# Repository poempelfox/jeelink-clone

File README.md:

# Foxis JeeLink-clone

## Intro

JeeLinks are transceivers with a microcontroller, that can be
attached to the USB port of a PC. They were designed many
years ago by JeeLabs a.k.a. Jean-Claude Wippler, and like all
of the (many!) cool designs on his now sadly defunct weblog
under jeelabs.org, they were completely Open-Source-Hardware -
while there was a webshop where you could buy ready-made
JeeLinks if you were lazy, you could also just build them
yourself, or modify the designs.

I use many JeeLinks as receivers for my various "FoxTemp"
sensors like foxtemp2016 or foxtemp2024. For that, the
JeeLink is flashed with the "LaCrosse" sketch developed
by the FHEM project (with one minor source code modification
needed to adapt the settings) and attached to a PC, where
a little deamon makes the received data available for query
via network.

Unfortunately, by now jeelabs.org is completely defunct and
you can only access the treasure trove of information that used
to be hosted there through archive.org. The webshop is still
there, but it is in the UK - and thanks to Brexit, ordering
from there to mainland Europe promises to be so painful that
I want to avoid it at all cost.

So where do I get my JeeLinks now?
Well the plan is to do what I've been doing a lot recently:
Design a PCB with mostly SMD components on one side, and
send it off to china for fabrication. And you may ask,
"Wait, doesn't that have the same problems as ordering
from the UK?", and of course in both cases it means crossing
the border from outside the EU into the EU taxation and
customs union. The difference is that the chinese fab
is registered as a so called IOSS, Import One Stop Shop.
That means (as of July 2024) that for any orders below 150
Euro the shop will directly collect the applicable VAT
and transfer it to EU customs. As orders below 150 Euro
are exempt from taxes other than VAT, that means everything
has already been paid when your parcel enters the EU.
And that makes a huge difference, because most parcel services
massively rip you off with the tax handling. For example,
DHL Express will charge a "Kapitalbereitstellungs-
Provision" of (at least) a whopping 14.88 Euros, even if
there was just a single cent of VAT to be paid for the
import, for borrowing you the money for two days. It's
also not possible to opt out of their shitty disservice
and just collect the parcel yourself at the next customs
office. But if there is no VAT or other taxes to be
paid, your parcel just arrives without the ripoff.

Note that this is NOT a full JeeLink clone. My goal
was to have something that works with the FHEM-LaCrosse-
Sketch so I don't have to touch that firmware. But
apart from that, I saw no reason to stay too true to
the original,  so a few modifications have been made:
- proper JeeLinks also have an extra 16 Mbit flash
  memory chip. That is not used by the LaCrosse sketch,
  so I left it out.
- JeeLinks have an ultrabright blue LED that massively
  annoyed me (I don't like getting blind from accidently
  looking at the stick. I also don't need it to
  illuminate the whole room.), so it was replaced with
  a very ordinary and certainly not ultrabright yellow
  LED.
- this did not import the old design files (which were
  in a very old Eagle file format that I couldn't get
  imported) and instead started from scratch in Kicad,
  so the positioning of things like LEDs is entirely
  different.
- When these things come from the factory, they have
  no bootloader that would permit programming them via
  USB yet. So we need to use ISP, but a normal-sized ISP
  connector is way too large to fit, and I didn't want to
  construct my own adapter. So instead, I put a
  "Tag-Connect" 6 pin connector there that is
  easily temporarily attachable with one of their
  cables. Unfortunately, these cables are very
  expensive, but they seem to work quite well.  
- I wanted the ability to attach either a wire antenna
  (like on normal JeeLinks) or something better, so
  it's optionally possible to solder on an SMA
  connector. However, my first tests indicate that
  this is not worth it - it does not improve reception
  that much, at least not in my usecases. And you
  will have to drill a big hole into the case if
  you want to use that.

Current status: A revision 0 was ordered from JLCPCB.
Unfortunately, it contained a very dumb mayor error,
that made it completely non-functional. So a
revision 1 was ordered, that fixed the mayor flaw and
also made some improvements to the outer dimensions
to better fit the case. This revision seems to work
very well. This project is now considered finished.

For your entertainment, here is a picture of the
botched repair of a revision 0 board to make it
work:

## Hardware

This consists of a board with an ATMEGA328P AVR,
an FT232RL USB-to-serial converter chip, and some
other minor parts like LEDs, caps and resistors
that I will not list here - take a look at the
Kicad files, or the "BOM"-file in the production
data. This board was assembled by a cheap SMT PCB
fab, namely JLCPCB. Note that the board is so small
that it actually violates their recommended error
margins in quite a few places, like distance of
soldering pads from the edge of the board, so if
things go badly, you might have problems with e.g.
cut pads and you really can't complain about that.
I was really counting on the fact that they are
usually far better than they claim to be, and it
worked out for me.

Besides the ready made boards, there are three
additional parts that would be very expensive to
assemble at JLCPCB because they are not standard
SMT parts, so these were soldered on manually
later. These parts are:

* a HopeRF RFM69CW wireless radio module
* a Molex 48037-2200 USB (USB-A) connector
* either a 82mm wire antenna, or a SMA connector
  (I used Adafruit 1865) for connecting up an
  external antenna

Optional but highly recommended is also a case.
The whole thing was designed so it fits into
a Bud Industries USB-7201-C enclosure. (The original
Jeelink also used either that or something that
looked VERY similiar.) This enclosure does have a
small hole at the end that is obviously intended
to attach a lanyard, however we can abuse this to
get the small wire antenna out of the case, and the
soldering point for the wire antenna has been
strategically placed for this.
Unfortunately this hole actually has a plastic tube
going through all the way from one side to the other,
so you'll have to break a little bit of the plastic
to get the wire in - the picture below shows how I
did this with a cutter. You really don't need to
break out the whole thing, just enough for the wire
to get through.

Finally, this is how it looks like when fully assembled,
without the enclosure on the left, and with the
enclosure on the right:

## Programming

As this will arrive without any bootloader, there
really is no way to get any firmware onto this
thing without doing ISP programming of the AVR chip
on the board at least once.

You then have the choice to either directly program
the main firmware you want to put on it via ISP, or
instead program the
["Optiboot" bootloader](https://github.com/Optiboot/optiboot),
that will then allow you to reprogram the main firmware
as often as you like over USB, but cost you 512 bytes
of Flash space.

Note that the 'VCC' pin on the ISP connector of the
board is not connected. You will therefore need to
power the board through USB even for the ISP programming.
You also need to make really sure your programmer is set
to 3.3V, else you will fry the radio module.

I used my trusty old STK500 (with v2 firmware) to
program Optiboot. You will need to adapt the below for
other programmers. The sequence I used was:

<pre>cd optibootcheckoutdir/optiboot/bootloaders/optiboot
make LED=B1 AVR_FREQ=16000000 BAUD_RATE=57600 LED_START_FLASHES=5 atmega328
avrdude -c stk500v2 -P /dev/ttyUSB0 -p m328p -e -u -U lock:w:0xEF:m -U efuse:w:0xFD:m -U hfuse:w:0xDE:m -U lfuse:w:0xFF:m -U flash:w:optiboot_atmega328.hex -U lock:w:0xEF:m</pre>

After that, this thing basically behaves like a normal
Jeelink would, and flashing the main firmware on was simply
done via its own USB port (for avrdude this is an "arduino"
programmer at 57600 baud).

## Files

You can find the Kicad files in [the kicad directory of this repository](./kicad/foxis-jeelink-clone/).

The production files (GERBER, BOM, CPL) that were sent to JLCPCB are in [the jlcpcb/production_files subdirectory](./kicad/foxis-jeelink-clone/jlcpcb/production_files/).

Finally, so you don't have to open Kicad just to take a quick look, there is a PDF of the schematic and of the PCB in [the pdf directory](./pdf/). There are also two images from the 3D viewer in Kicad: [3D viewer front](./pics/foxis-jeelink-clone-3dv-front.png) [3D viewer back](./pics/foxis-jeelink-clone-3dv-back.png).

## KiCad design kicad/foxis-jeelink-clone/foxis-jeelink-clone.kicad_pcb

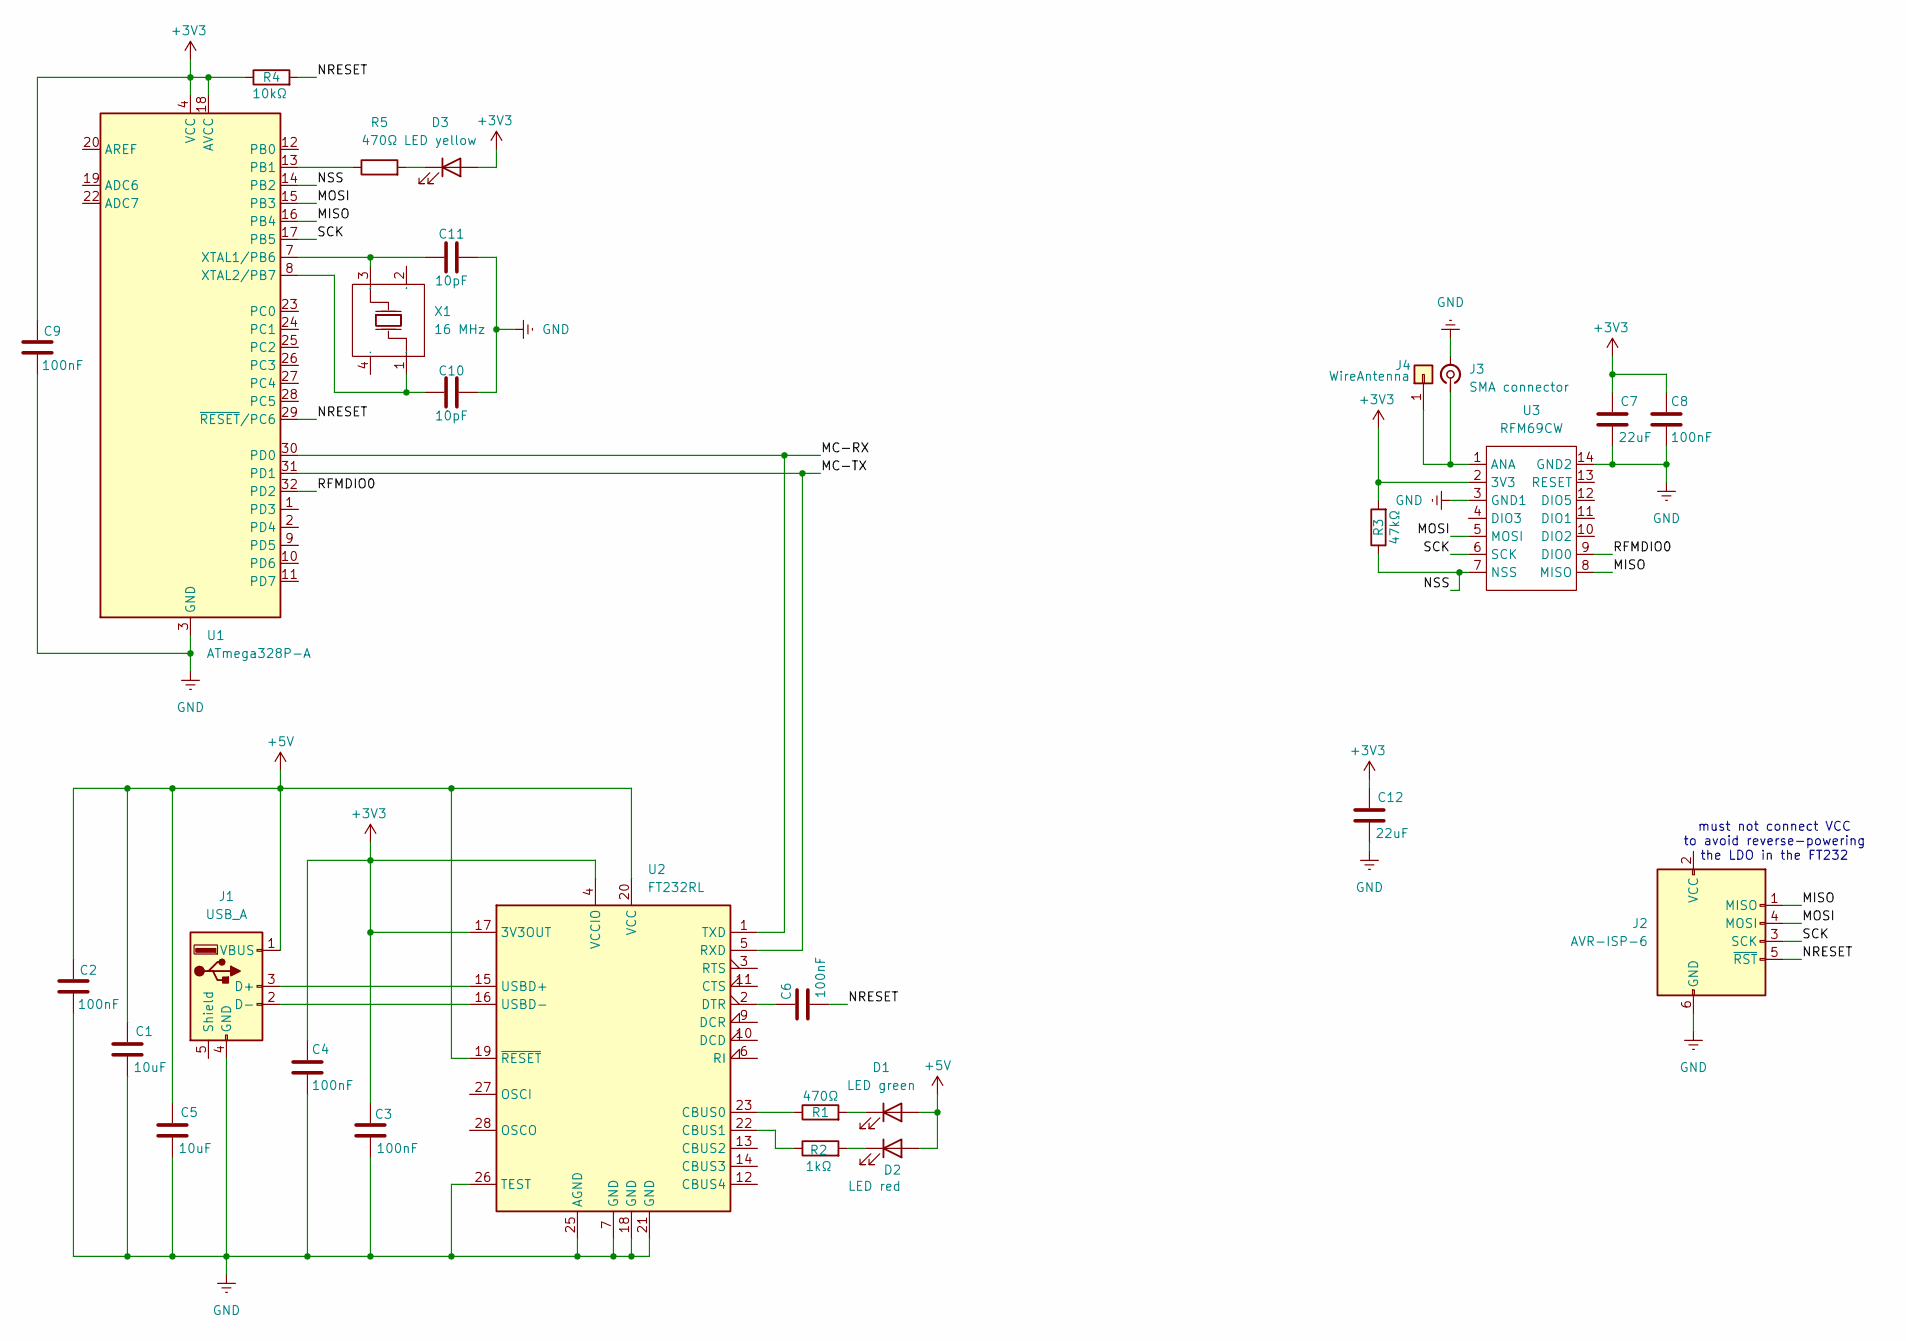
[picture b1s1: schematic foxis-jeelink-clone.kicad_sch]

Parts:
C1, C5: 10uF; C_0603_1608Metric
C2, C3, C4, C6, C8, C9: 100nF; C_0402_1005Metric
C7, C12: 22uF; C_0603_1608Metric
C10, C11: 10pF; C_0402_1005Metric
D1: LED green; LED_0805_2012Metric
D2: LED red; LED_0603_1608Metric
D3: LED yellow; LED_0603_1608Metric
J1: USB_A; USB_A_Molex_48037-2200_Horizontal
J2: AVR-ISP-6; Tag-Connect_TC2030-IDC-NL_2x03_P1.27mm_Vertical
J3: SMA connector; SMA_Samtec_SMA-J-P-X-ST-EM1_EdgeMount
J4: WireAntenna; SolderWire-0.25sqmm_1x01_D0.65mm_OD2mm
R1, R5: 470Ω; R_0402_modsilkscreen
R2: 1kΩ; R_0402_modsilkscreen
R3: 47kΩ; R_0402_modsilkscreen
R4: 10kΩ; R_0402_modsilkscreen
U1: ATmega328P-A; TQFP-32_7x7mm_P0.8mm
U2: FT232RL; SSOP-28_5.3x10.2mm_P0.65mm
U3: RFM69CW; HOPERF_RFM69CW
X1: 16 MHz; OSC-SMD_4P-L3.2-W2.5-BL

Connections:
+3V3: C3.1, C4.1, C7.1, C8.1, C9.1, C12.1, D3.2 (A), R3.2, R4.1, U1.4 (VCC), U1.6 (VCC), U1.18 (AVCC), U2.4 (VCCIO), U2.17 (3V3OUT), U3.2 (3V3)
+5V: C1.1, C2.1, C5.1, D1.2 (A), D2.2 (A), J1.1 (VBUS), U2.19 (~RESET), U2.20 (VCC)
/MC-RX: U1.30 (PD0), U2.1 (TXD)
/MC-TX: U1.31 (PD1), U2.5 (RXD)
/MISO: J2.1 (MISO), U1.16 (PB4), U3.8 (MISO)
/MOSI: J2.4 (MOSI), U1.15 (PB3), U3.5 (MOSI)
/NRESET: C6.2, J2.5 (~RST), R4.2, U1.29 (~RESET/PC6)
/NSS: R3.1, U1.14 (PB2), U3.7 (NSS)
/RFMDIO0: U1.32 (PD2), U3.9 (DIO0)
/SCK: J2.3 (SCK), U1.17 (PB5), U3.6 (SCK)
GND: C1.2, C2.2, C3.2, C4.2, C5.2, C7.2, C8.2, C9.2, C10.1, C11.2, C12.2, J1.4 (GND), J2.6 (GND), J3.2 (Ext), U1.3 (GND), U1.5 (GND), U1.21 (GND), U2.7 (GND), U2.18 (GND), U2.21 (GND), U2.25 (AGND), U2.26 (TEST), U3.3 (GND1), U3.14 (GND2)
unnamed: D1.1 (K), R1.2
unnamed: D2.1 (K), R2.2
unnamed: D3.1 (K), R5.2
unnamed: J1.3 (D+), U2.15 (USBD+)
unnamed: J1.2 (D-), U2.16 (USBD-)
unnamed: J3.1 (In), J4.1, U3.1 (ANA)
unnamed: R5.1, U1.13 (PB1)
unnamed: C11.1, U1.7 (XTAL1/PB6), X1.3 (OSC2)
unnamed: C10.2, U1.8 (XTAL2/PB7), X1.1 (OSC1)
unnamed: R1.1, U2.23 (CBUS0)
unnamed: R2.1, U2.8, U2.22 (CBUS1)
unnamed: C6.1, U2.2 (DTR)

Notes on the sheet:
must not connect VCC to avoid reverse-powering the LDO in the FT232

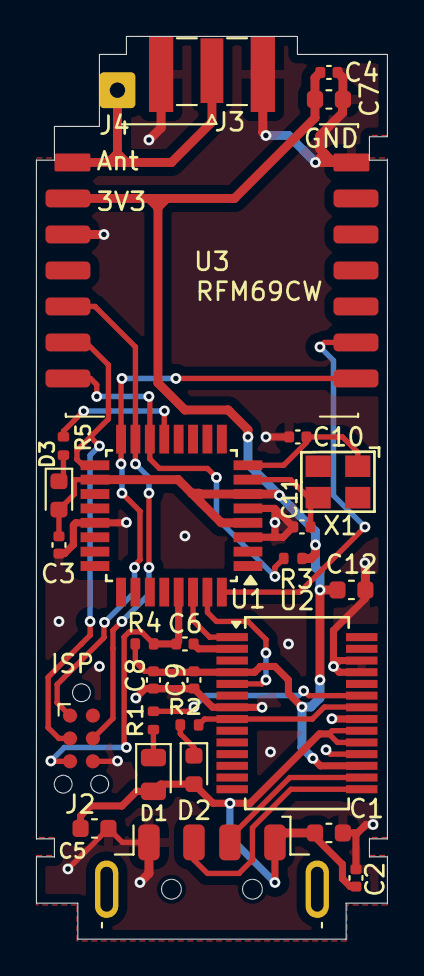
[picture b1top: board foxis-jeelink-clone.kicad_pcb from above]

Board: 2 copper layers, 19.5 x 50.2 mm, 28 parts (0 on the bottom side), 23 nets.

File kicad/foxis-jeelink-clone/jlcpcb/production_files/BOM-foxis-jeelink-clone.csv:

Comment,Designator,Footprint,LCSC
C1,10uF,C_0603_1608Metric,C19702,5879468,0,0
C10,10pF,C_0402_1005Metric,C32949,890161,0,0
C11,10pF,C_0402_1005Metric,C32949,890161,0,0
C12,22uF,C_0603_1608Metric,C59461,7095416,0,0
C2,100nF,C_0402_1005Metric,C1525,26786529,0,0
C3,100nF,C_0402_1005Metric,C1525,26786529,0,0
C4,100nF,C_0402_1005Metric,C1525,26786529,0,0
C5,10uF,C_0603_1608Metric,C19702,5879468,0,0
C6,100nF,C_0402_1005Metric,C1525,26786529,0,0
C7,22uF,C_0603_1608Metric,C59461,7095416,0,0
C8,100nF,C_0402_1005Metric,C1525,26786529,0,0
C9,100nF,C_0402_1005Metric,C1525,26786529,0,0
D1,LED green,LED_0805_2012Metric,C2297,1323534,0,0
D2,LED red,LED_0603_1608Metric,C2286,3092699,0,0
D3,LED yellow,LED_0603_1608Metric,C72038,533560,0,0
R1,470Ω,R_0402_modsilkscreen,C25117,2703821,0,0
R2,1kΩ,R_0402_modsilkscreen,C11702,7995538,0,0
R3,47kΩ,R_0402_modsilkscreen,C25792,891377,0,0
R4,10kΩ,R_0402_modsilkscreen,C25744,8806732,0,0
R5,470Ω,R_0402_modsilkscreen,C25117,2703821,0,0
U1,ATmega328P-A,TQFP-32_7x7mm_P0.8mm,C14877,19962,0,0
U2,FT232RL,SSOP-28_5.3x10.2mm_P0.65mm,C8690,4578,0,0
X1,16 MHz,OSC-SMD_4P-L3.2-W2.5-BL,C13738,102528,0,0

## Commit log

2024-07-19 Rev. 0 as sent to JLCPCB.
2024-07-19 small status update
2024-07-31 fix massive error that made Rev. 0 completely nonfunctional. I simply forgot to connect RX and TX. Absolutely no idea how I managed to mess this up.
2024-08-03 status update
2024-08-10 more text and two pictures
2024-08-10 more pictures and description
2024-08-10 rev. 1 as sent to JLCPCB
2024-08-11 explain how to get the wire antenna out of the case.
2024-08-12 add PDF and screenshot of 3D viewer
2024-08-12 fix broken link
